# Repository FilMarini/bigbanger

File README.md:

# BigBanger :boom:

BigBanger is an ESP32-based open-source project that combines firmware and hardware to create a Bluetooth-enabled scale, mainly designed for climbing training.

The firmware can be chosen between *micropython*, easy to read and customize, but poorer power consumption, or *rust*, where it gets a bit more complicated but improves the efficiency.

This scale is fully compatible with the [Tindeq Progressor API](https://tindeq.com/progressor_api/), enabling easy integration with apps that support them, including the official Tindeq Progressor app.

The BigBanger board is designed to exploit the housing of cheap scales that you can buy on Amazon/Aliexpress.

Currently, the supported housing are:

* [WeiHeng WH-C07](https://it.aliexpress.com/item/1005004488455473.html?spm=a2g0o.productlist.main.45.6640ebyYebyYDH&algo_pvid=4eb4987b-360f-48ef-b21f-248b90a92ae2&algo_exp_id=4eb4987b-360f-48ef-b21f-248b90a92ae2-22&pdp_npi=4%40dis%21EUR%2122.65%2113.59%21%21%2122.91%2113.75%21%40210388c917363545957476762e73f7%2112000029333412625%21sea%21IT%21185384505%21X&curPageLogUid=mN6PXk7hKujt&utparam-url=scene%3Asearch%7Cquery_from%3A)
* [WeiHeng WH-C100](https://it.aliexpress.com/item/1005007661854154.html?spm=a2g0o.productlist.main.17.6640KMtfKMtfLb&algo_pvid=460fc652-4241-4711-9569-1d04a7b966ac&algo_exp_id=460fc652-4241-4711-9569-1d04a7b966ac-8&pdp_npi=4%40dis%21EUR%2137.58%2118.79%21%21%21276.32%21138.16%21%40210384b217385760281077417e6aa7%2112000041701557701%21sea%21IT%21185384505%21X&curPageLogUid=ai0LjxSLr64K&utparam-url=scene%3Asearch%7Cquery_from%3A)

This is not the first open-source Tindeq Progressor-like project. The [hangman](https://github.com/kesyog/hangman) is a very similar example. BigBanger was developed from scratch as a personal learning experience.

## Repository structure

* **firmware**:
  * *upython* contains the micropython firmware for the ESP32-C3
  * *rust* contains the rust firmware for the ESP32-C3

* **hardware**: contains the Kicad project for the PCB

## Prerequisite

### Micropython

* Python 3.7 or newer

* [esptool](https://docs.espressif.com/projects/esptool/en/latest/esp32/index.html)

* [rshell](https://github.com/dhylands/rshell)

### Rust

* Rust toolchain and tooling installation compatible with ESP32-C3. Please follow the steps outlined [here](https://docs.espressif.com/projects/rust/book/getting-started/toolchain.html)

## How-to Hardware

1. Build the PCB from the Kicad project. Design is fully compliant with [JLCPCB rules](https://jlcpcb.com/capabilities/pcb-capabilities)

    * The JLCPCB gerbers and assembly files are available in the [release page](https://github.com/FilMarini/bigbanger/releases/tag/v1.2)

    * If you assemble the PCB with JLCPCB, go to step 3

2. Buy the components. [Here](https://www.digikey.it/it/mylists/list/KCSV7UEBPS) is a full Digikey list of parts

3. Get to soldering!

    Battery wiring:
    
    * B+: Red
    * B-: Black

    Load cell wiring:
    
    * E-: Black
    * A-: White
    * A+: Green
    * E+: Red

4. Turn on the BigBanger and connect to PC using the microUSB

    * Device should appear as `/dev/ttyACM*` or `/dev/ttyUSB*`

## How-to Firmware

### Micropython

1. Flash the ESP32-C3 micropython firmware. Instructions and firmware files are [here](https://micropython.org/download/ESP32_GENERIC_C3/)

2. Copy the `.py` files in the 'firmware/upython' folder into the ESP32. Copy the `hx711/hx711_gpio.py` file into the ESP32. For this you can use [rshell](https://github.com/dhylands/rshell)

   * Modify the `main.py` file. You need to specify the Bluetooth name for your device (If you want it compatible with the Tindeq Progressor, name must start with `Progressor`) as well as the crane scale used (Supported values are `WH-C07` and `WH-C100`)

    * With [rshell](https://github.com/dhylands/rshell):
    
       ```bash
       git clone --recursive https://github.com/FilMarini/bigbanger.git
       cd bigbanger/firmware/upython
       rshell -p /dev/tty<your device> cp bb_gatt_server.py ble_advertising.py config.py hx711_bb.py utils.py hx711/hx711_gpio.py main.py /pyboard # Probably requires sudo privileges
       ```

3. Start training!

### Rust

1. Install the rust toolchain for ESP32-C3. Please follow the [guide](https://docs.espressif.com/projects/rust/book/getting-started/toolchain.html)

1. If you want to modify the Bluetooth advertisement name, change it in [firmware/rust/.cargo/config.toml](https://github.com/FilMarini/bigbanger/blob/rust/firmware/rust/.cargo/config.toml#L26) under `PROGRESSOR_NAME`. Bear in mind that the advertised name must start with `Progressor_` in order to be recognized from the Tindeq App.

2. Once the toolchain is set up, go into the Rust firmware directory and build in release mode:

   ```bash
   cd firmware/rust
   cargo build --release
   ```
   
4. With the BigBanger connected, flash the firmware:

   ```bash
   cargo run --release
   ```
   
6. Start training!

## Calibration

The BigBanger scale comes pre-calibrated, but if for any reason the calibration is lost, you can recalibrate it using the built-in two-point calibration system. This system requires two weight measurements with a 10 kg difference—typically one at zero weight and another at 10 kg.

### How to calibrate

- Turn on the BigBanger scale and ensure it is disconnected from any device.

- Press and hold the Unit button until the LED D5 turns on (this takes a few seconds).

- When the LED turns on, the scale performs the first measurement (normally at zero weight).

- Add 10 kg weight on the scale.

- Press the Unit button again. The LED D5 should turn off.

- The scale is now calibrated and you can now connect to it.

## Acknowledgements

Huge thanks to [Tindeq](https://tindeq.com/product/progressor/) for improving climbing training for all of us with their innovative product and for making their API available to third-party developers, enabling projects like this one. If you find this useful, consider supporting them by getting one of their products—they’re well worth it!

Special thanks also to [kesyog](https://github.com/kesyog) for their excellent open-source project [hangman](https://github.com/kesyog/hangman), which provided valuable guidance and inspiration for the Rust firmware implementation. Since I started with zero Rust knowledge, having a working example to learn from was incredibly helpful — some parts of the code resemble the original hangman implementation.

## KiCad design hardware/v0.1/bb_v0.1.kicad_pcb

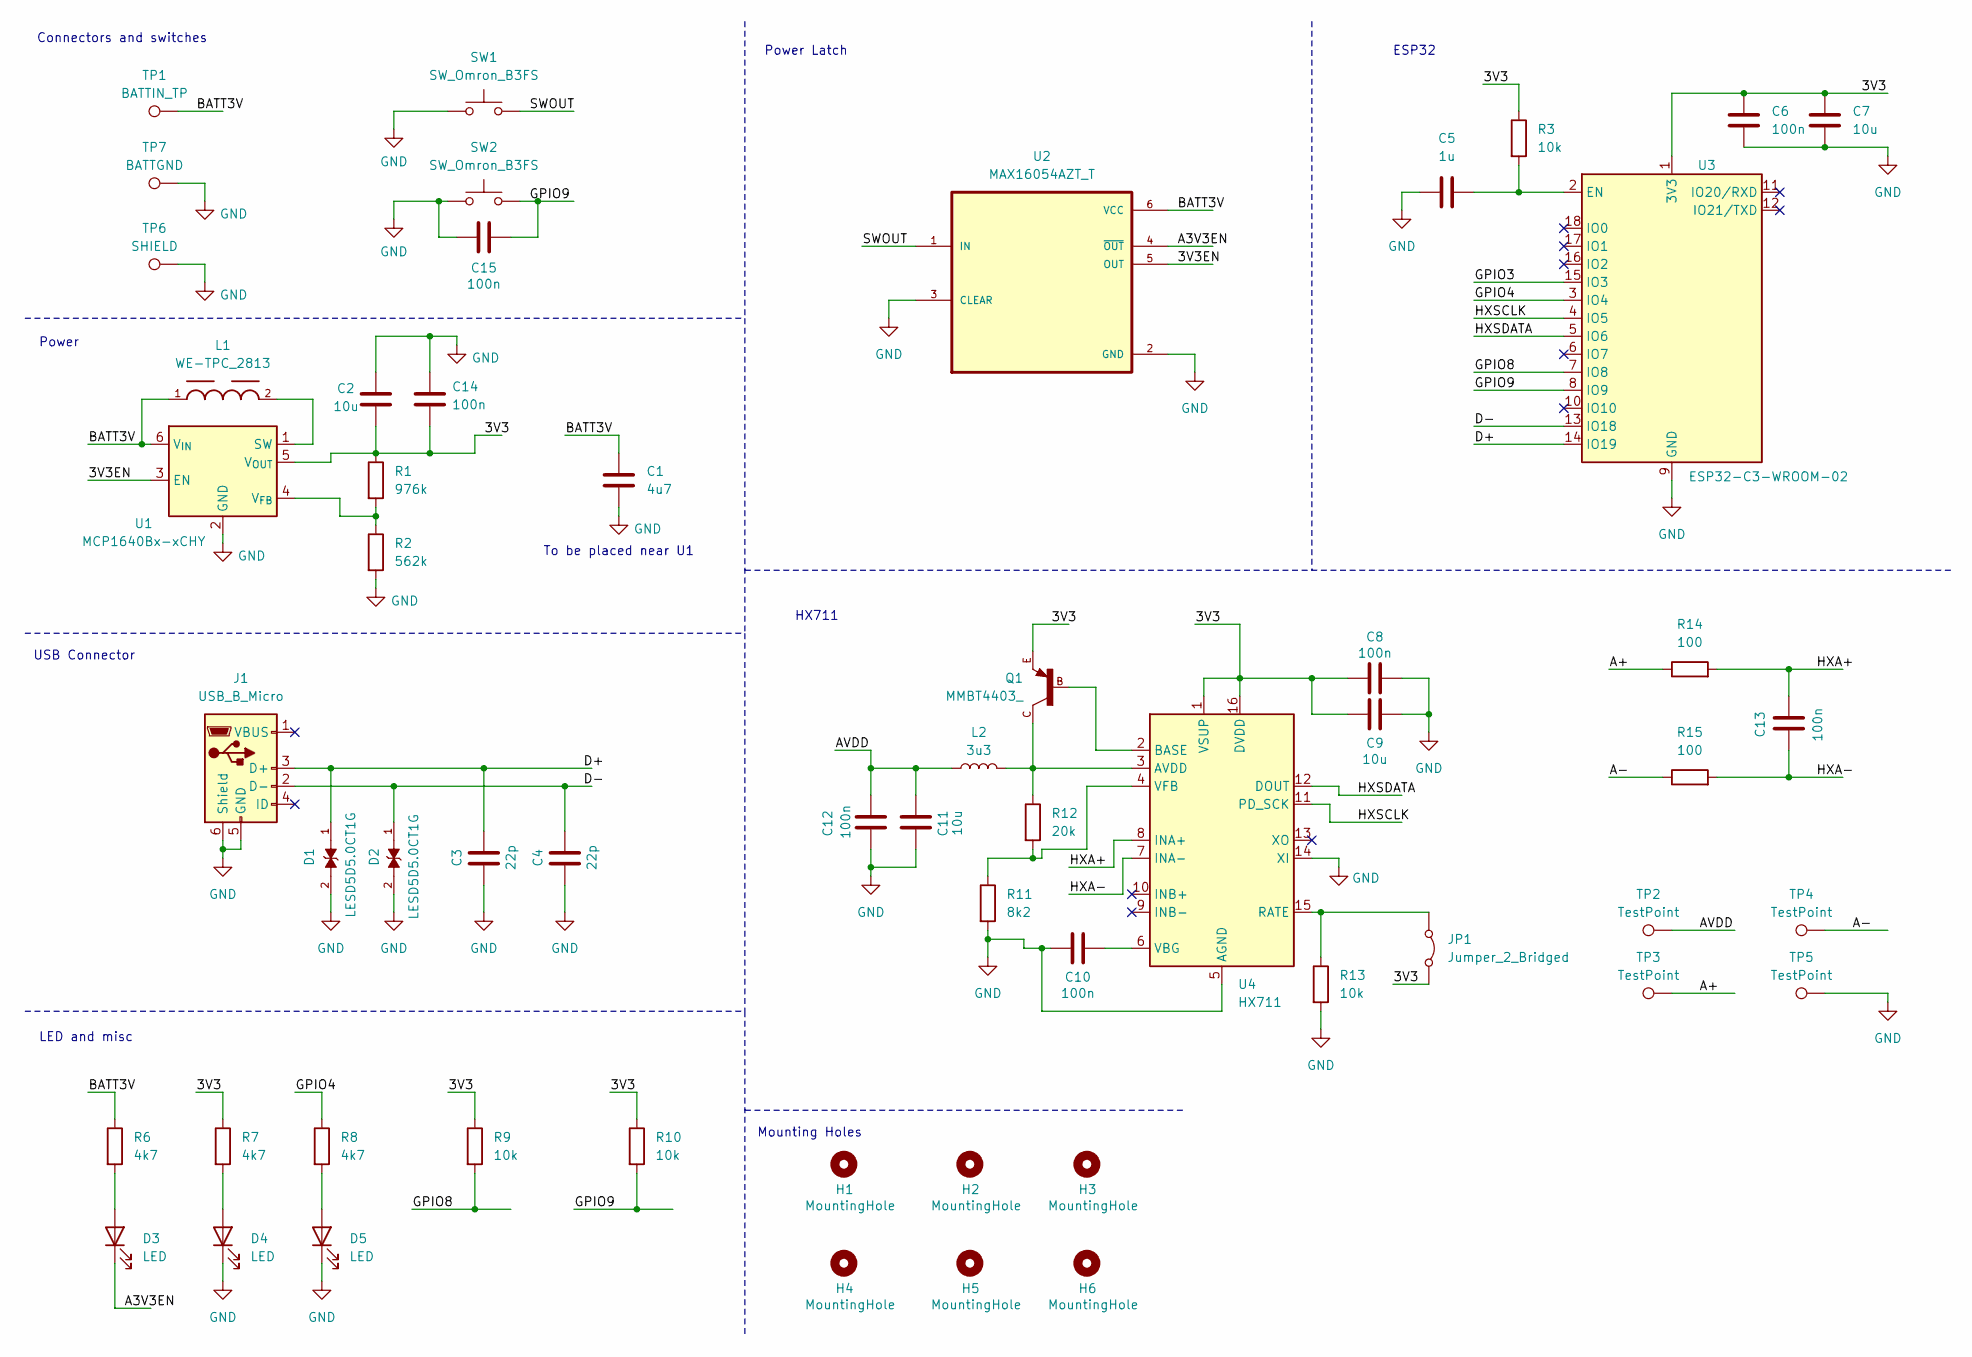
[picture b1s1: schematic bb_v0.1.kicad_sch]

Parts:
C1: 4u7; C_0603_1608Metric_Pad1.08x0.95mm_HandSolder
C2, C7, C9, C11: 10u; C_0603_1608Metric_Pad1.08x0.95mm_HandSolder
C3, C4: 22p; C_0603_1608Metric_Pad1.08x0.95mm_HandSolder
C5: 1u; C_0603_1608Metric_Pad1.08x0.95mm_HandSolder
C6, C8, C10, C12, C13, C14, C15: 100n; C_0603_1608Metric_Pad1.08x0.95mm_HandSolder
D1, D2: LESD5D5.0CT1G; TVS_LESD5D5.0CT1G; PARTREV O
D3, D4, D5: LED; LED_0603_1608Metric_Pad1.05x0.95mm_HandSolder
H1, H2, H3, H4, H5, H6: MountingHole; MountingHole_2.2mm_M2
J1: USB_B_Micro; USB_Micro-B_Amphenol_10118194-0001LF_Horizontal
JP1: Jumper_2_Bridged; SolderJumper-2_P1.3mm_Open_RoundedPad1.0x1.5mm
L1: WE-TPC_2813; DigiKey_Part_Number 732-1089-2-ND
L2: 3u3; L_0603_1608Metric_Pad1.05x0.95mm_HandSolder
Q1: MMBT4403_; SOT23-BEC
R1: 976k; R_0603_1608Metric_Pad0.98x0.95mm_HandSolder
R2: 562k; R_0603_1608Metric_Pad0.98x0.95mm_HandSolder
R3, R9, R10, R13: 10k; R_0603_1608Metric_Pad0.98x0.95mm_HandSolder
R6, R7, R8: 4k7; R_0603_1608Metric_Pad0.98x0.95mm_HandSolder
R11: 8k2; R_0603_1608Metric_Pad0.98x0.95mm_HandSolder
R12: 20k; R_0603_1608Metric_Pad0.98x0.95mm_HandSolder
R14, R15: 100; R_0603_1608Metric_Pad0.98x0.95mm_HandSolder
SW1, SW2: SW_Omron_B3FS; SW_SPST_Omron_B3FS-101xP
TP1: BATTIN_TP; TestPoint_Pad_2.0x2.0mm
TP2, TP3, TP4, TP5: TestPoint; TestPoint_Pad_2.0x2.0mm
TP6: SHIELD; TestPoint_Pad_2.0x2.0mm
TP7: BATTGND; TestPoint_Pad_2.0x2.0mm
U1: MCP1640Bx-xCHY; SOT-23-6
U2: MAX16054AZT_T; SOT95P275X110-6N
U3: ESP32-C3-WROOM-02
U4: HX711; SOP-16_3.9x9.9mm_P1.27mm

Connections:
/3V3: C2.2, C6.2, C7.2, C8.1, C9.1, C14.2, JP1.2 (B), Q1.E, R1.1, R3.1, R7.1, R9.1, R10.1, U1.5 (V_{OUT}), U3.1 (3V3), U4.1 (VSUP), U4.16 (DVDD)
/3V3EN: U1.3 (EN), U2.5 (OUT)
/A3V3EN: D3.1 (K), U2.4 (~OUT)
/A+: R14.1, TP3.1
/A-: R15.1, TP4.1
/AVDD: C11.2, C12.2, L2.1, TP2.1
/BATT3V: C1.1, L1.1, R6.1, TP1.1, U1.6 (V_{IN}), U2.6 (VCC)
/D+: C3.1, D1.1, J1.3 (D+), U3.14 (IO19)
/D-: C4.1, D2.1, J1.2 (D-), U3.13 (IO18)
/GPIO3: U3.15 (IO3)
/GPIO4: R8.1, U3.3 (IO4)
/GPIO8: R9.2, U3.7 (IO8)
/GPIO9: C15.2, R10.2, SW2.2, U3.8 (IO9)
/HXA+: C13.2, R14.2, U4.8 (INA+)
/HXA-: C13.1, R15.2, U4.7 (INA-)
/HXSCLK: U3.4 (IO5), U4.11 (PD_SCK)
/HXSDATA: U3.5 (IO6), U4.12 (DOUT)
/SWOUT: SW1.2, U2.1 (IN)
GND: C1.2, C2.1, C3.2, C4.2, C5.1, C6.1, C7.1, C8.2, C9.2, C10.1, C11.1, C12.1, C14.1, C15.1, D1.2, D2.2, D4.1 (K), D5.1 (K), J1.5 (GND), J1.6 (Shield), R2.2, R11.2, R13.2, SW1.1, SW2.1, TP5.1, TP6.1, TP7.1, U1.2 (GND), U2.2 (GND), U2.3 (CLEAR), U3.9 (GND), U3.19 (GND), U4.5 (AGND), U4.14 (XI)
unnamed: D3.2 (A), R6.2
unnamed: D4.2 (A), R7.2
unnamed: D5.2 (A), R8.2
unnamed: JP1.1 (A), R13.1, U4.15 (RATE)
unnamed: L1.2, U1.1 (SW)
unnamed: R1.2, R2.1, U1.4 (V_{FB})
unnamed: C5.2, R3.2, U3.2 (EN)
unnamed: L2.2, Q1.C, R12.1, U4.3 (AVDD)
unnamed: Q1.B, U4.2 (BASE)
unnamed: C10.2, U4.6 (VBG)
unnamed: R11.1, R12.2, U4.4 (VFB)

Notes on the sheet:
LED and misc
USB Connector
ESP32
Power
Mounting Holes
Connectors and switches
Power Latch
HX711
To be placed near U1

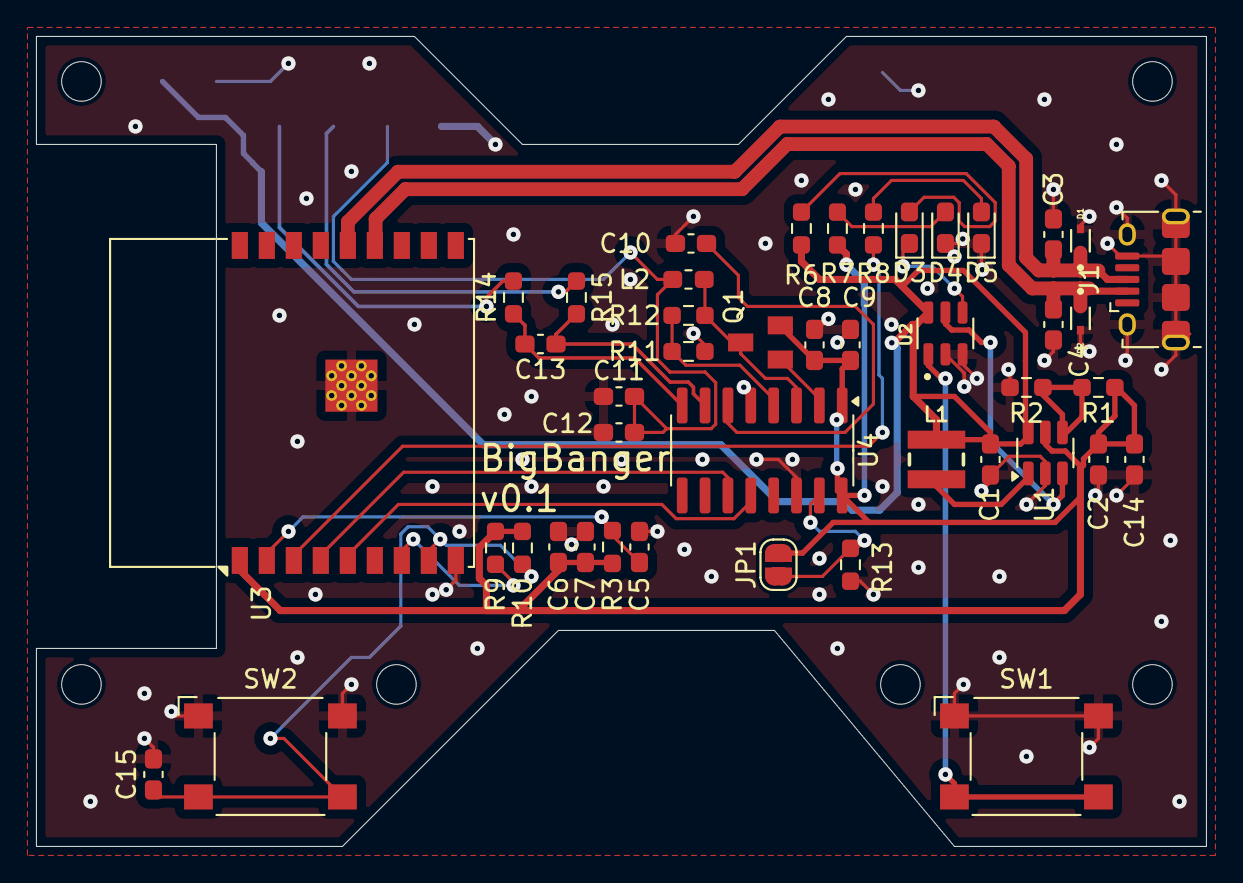
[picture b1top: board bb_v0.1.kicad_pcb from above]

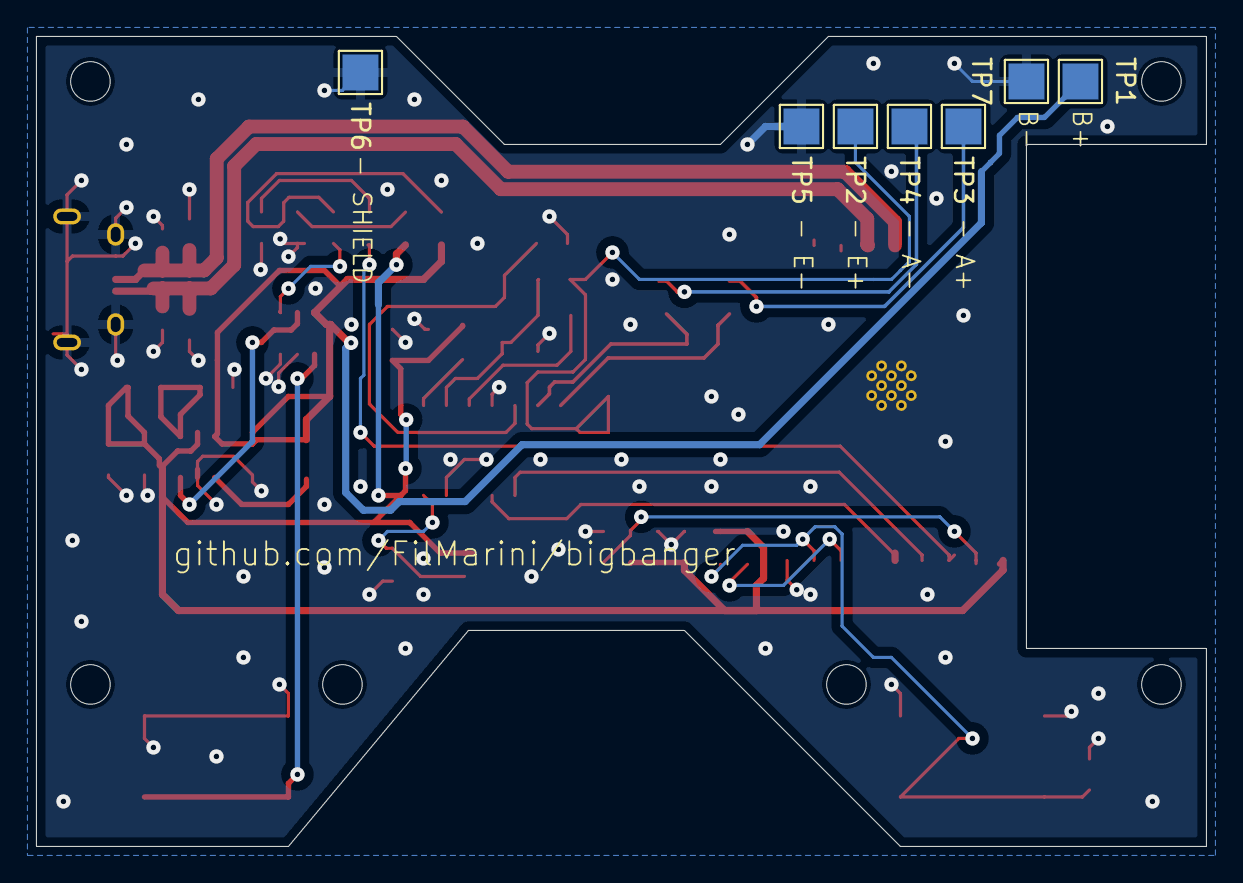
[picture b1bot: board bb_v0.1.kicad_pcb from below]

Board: 2 copper layers, 65.0 x 45.0 mm, 57 parts (7 on the bottom side), 29 nets.

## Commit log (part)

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2025-01-06 first firmware commit
2025-01-06 sending random data
2025-01-06 added tare scale
2025-01-07 add device id
2025-01-07 first hardware commit
2025-01-07 changed adv name
2025-01-07 Create LICENSE
2025-01-07 first commit of full schematic
2025-01-07 fixed schematic
2025-01-08 first complete layout
2025-01-08 added button
2025-01-08 first version complete layout
2025-01-08 added README
2025-01-09 moved kicad project location to show supported housings
2025-01-09 checked measures
2025-01-09 first design submitted
2025-01-10 connected to load cell
2025-01-10 added hx711 submodule
2025-01-10 need to pack several readings together to avoid bugs
2025-01-10 using different hx711 lib
2025-01-10 using built-in methods to read values
2025-01-24 changed kicad project location
2025-01-24 scale factor updated for WH-C07
2025-01-25 fixed oversights after first iteration
2025-02-03 v1.0
2025-02-03 added bb photo
2025-02-03 added acknoledgements
2025-02-03 changed project name and version
2025-02-04 first implementation of tare mode
2025-02-04 changed time.sleep to asyncio.wait
2025-02-04 first attempt to beautification
2025-02-04 fix stuff after sim
2025-02-04 changed a few constants for better import
2025-02-06 tested
2025-02-06 Code refactoring (#2)
2025-02-06 better tare
2025-02-06 fixed oversight
2025-02-13 first version with tare
2025-02-17 Change comment on calibration
2025-02-17 Remove tare after calibration
2025-02-18 add calibration instructions
2025-02-18 modified README
2025-02-18 Calibration mode (#3)
    Adding calibration mode to the BigBanger fw
2025-02-26 workaround for tare fix
2025-02-26 Tare fix (#4)
2025-03-09 Add better bb pictures
2025-10-21 moved upython firmware
2025-10-22 adding rust src files
2025-10-22 add gitignore
2025-10-22 Enhance README with Rust firmware information
    Updated README to include Rust firmware details and installation instructions.
2025-10-22 Change PROGRESSOR_NAME to 'Progressor_BB'
2025-10-23 Refine README formatting and instructions
    Updated formatting and clarified instructions for Micropython and Rust sections.
2025-10-23 Fix capitalization of 'microPython' and 'Rust' in README
